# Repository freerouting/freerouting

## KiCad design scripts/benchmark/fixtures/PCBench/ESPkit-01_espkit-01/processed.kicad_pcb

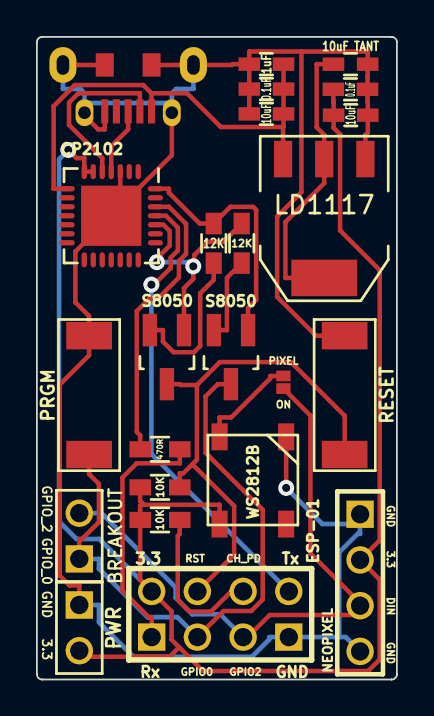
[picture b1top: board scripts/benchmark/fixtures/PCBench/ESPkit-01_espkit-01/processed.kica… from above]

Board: 2 copper layers, 20.0 x 35.7 mm, 24 parts (0 on the bottom side), 18 nets.

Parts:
C1, C6: 10uF; C_0603_HandSoldering
C4, C7: 0.1uF; C_0603_HandSoldering
C5: 1uF; C_0603_HandSoldering
C8: 10uF TANT; C_0603_HandSoldering
IC1: WS2812B; ws2812b
P1: ESP-01
P2: BREAKOUT; PIN_ARRAY_2X1
P3: USB_5PIN_SHELL; USB-MICRO-5pin_PTHMOUNT
P4: PWR; PIN_ARRAY_2X1
P5: NEOPIXEL; PIN_ARRAY_4x1
P6: BRIDGE; 603_bridge
Q1, Q2: S8050; SOT-23_Handsoldering
R1, R4: 10K; R_0603_HandSoldering
R2, R3: 12K; R_0603_HandSoldering
R5: 470R; R_0603_HandSoldering
SW1: RESET; 1107G
SW2: PRGM; 1107G
U1: LD1117; SOT-223
U2: CP2102; QFN-28-1EP_5x5mm_Pitch0.5mm

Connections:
+3.3V: C1.1, C4.1, IC1.1, P1.2, P4.2, P5.2, R1.2, R4.2, U2.6, U2.7
+3V3: C8.1, U1.2, U1.4
+5V: C5.1, C6.1, C7.1, P3.1, U1.3, U2.8
/DTR: Q2.1, R2.2, U2.28
/ESP_EN: P1.6, R1.1
/GPIO0: P1.3, P2.1, Q2.3, SW2.1
/GPIO2: P1.5, P2.2, P5.3, P6.2
/RESET: P1.4, Q1.3, R4.1, SW1.1
/RTS: Q1.1, R3.2, U2.24
/RXD: P1.8, U2.25
/TXD: P1.1, R5.1
/USB_D+: P3.3, U2.4
/USB_D-: P3.2, U2.5
GND: C1.2, C4.2, C5.2, C6.2, C7.2, C8.2, IC1.3, P1.7, P3.5, P3.SHLD, P4.1, P5.1, P5.4, SW1.2, SW2.2, U1.1, U2.3, U2.29
unnamed: IC1.4, P6.1
unnamed: Q1.2, R2.1
unnamed: Q2.2, R3.1
unnamed: R5.2, U2.26

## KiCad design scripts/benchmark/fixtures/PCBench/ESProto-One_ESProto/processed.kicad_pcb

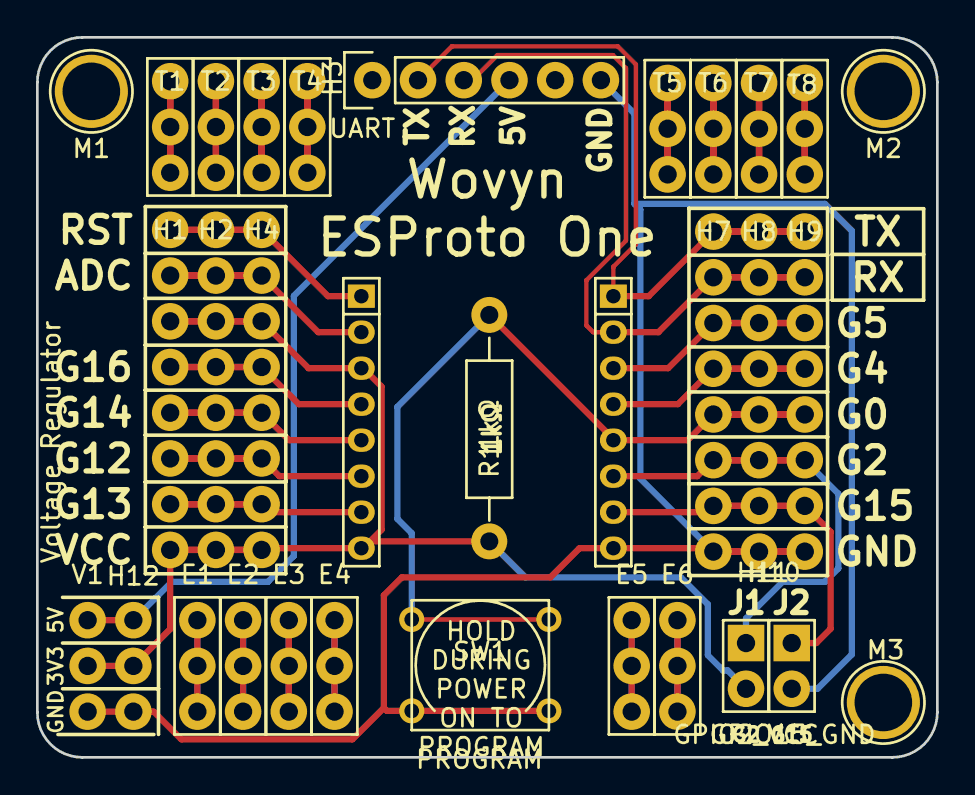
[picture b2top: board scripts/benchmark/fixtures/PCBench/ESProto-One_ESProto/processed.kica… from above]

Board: 2 copper layers, 50.0 x 40.0 mm, 32 parts (0 on the bottom side), 30 nets.

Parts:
E1: Ex1; Pin_Header_Straight_1x03
E2: Ex2; Pin_Header_Straight_1x03
E3: Ex3; Pin_Header_Straight_1x03
E4: Ex4; Pin_Header_Straight_1x03
E5: Ex5; Pin_Header_Straight_1x03
E6: Ex6; Pin_Header_Straight_1x03
H1: L3; Pin_Header_Straight_1x08
H2: L2; Pin_Header_Straight_1x08
H3: UART; Pin_Header_Straight_1x06
H4: L1; Pin_Header_Straight_1x08
H5: L0; Pin_Header_Straight_1x08_Pitch2.00mm
H6: R0; Pin_Header_Straight_1x08_Pitch2.00mm
H7: R1; Pin_Header_Straight_1x08
H8: R2; Pin_Header_Straight_1x08
H9: R3; Pin_Header_Straight_1x08
H10: GPIO15_GND; Pin_Header_Straight_1x02
H11: GPIO2_VCC; Pin_Header_Straight_1x02
H12: VRegOut; Pin_Header_Straight_1x03
M1, M2, M3: 1pin
R1: 1kΩ; Resistor_Horizontal_RM15mm
SW1: PROGRAM; SW_PUSH_SMALL
T1: T1; Pin_Header_Straight_1x03
T2: T2; Pin_Header_Straight_1x03
T3: T3; Pin_Header_Straight_1x03
T4: T4; Pin_Header_Straight_1x03
T5: T5; Pin_Header_Straight_1x03
T6: T6; Pin_Header_Straight_1x03
T7: T7; Pin_Header_Straight_1x03
T8: T8; Pin_Header_Straight_1x03
V1: Voltage_Regulator; Pin_Header_Straight_1x03

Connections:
+3V3: H1.3, H1.8, H2.3, H2.8, H4.3, H4.8, H5.3, H5.8, H11.2, H12.2, R1.1, V1.2
+5V: H3.4, H12.1, V1.1
GND: H3.6, H6.8, H7.8, H8.8, H9.8, H10.2, H12.3, SW1.2, V1.3
unnamed: E1.1, E1.2, E1.3
unnamed: E2.1, E2.2, E2.3
unnamed: E3.1, E3.2, E3.3
unnamed: E4.1, E4.2, E4.3
unnamed: E5.1, E5.2, E5.3
unnamed: E6.1, E6.2, E6.3
unnamed: H1.1, H2.1, H4.1, H5.1
unnamed: H1.2, H2.2, H4.2, H5.2
unnamed: H1.4, H2.4, H4.4, H5.4
unnamed: H1.5, H2.5, H4.5, H5.5
unnamed: H1.6, H2.6, H4.6, H5.6
unnamed: H1.7, H2.7, H4.7, H5.7
unnamed: H6.3, H7.3, H8.3, H9.3
unnamed: H6.4, H7.4, H8.4, H9.4
unnamed: H6.5, H7.5, H8.5, H9.5, R1.2, SW1.1
unnamed: H6.7, H7.7, H8.7, H9.7, H10.1
unnamed: H6.6, H7.6, H8.6, H9.6, H11.1
unnamed: T1.1, T1.2, T1.3
unnamed: T2.1, T2.2, T2.3
unnamed: T3.1, T3.2, T3.3
unnamed: T4.1, T4.2, T4.3
unnamed: T5.1, T5.2, T5.3
unnamed: T6.1, T6.2, T6.3
unnamed: T7.1, T7.2, T7.3
unnamed: T8.1, T8.2, T8.3
RXD: H3.3, H6.2, H7.2, H8.2, H9.2
TXD: H3.2, H6.1, H7.1, H8.1, H9.1

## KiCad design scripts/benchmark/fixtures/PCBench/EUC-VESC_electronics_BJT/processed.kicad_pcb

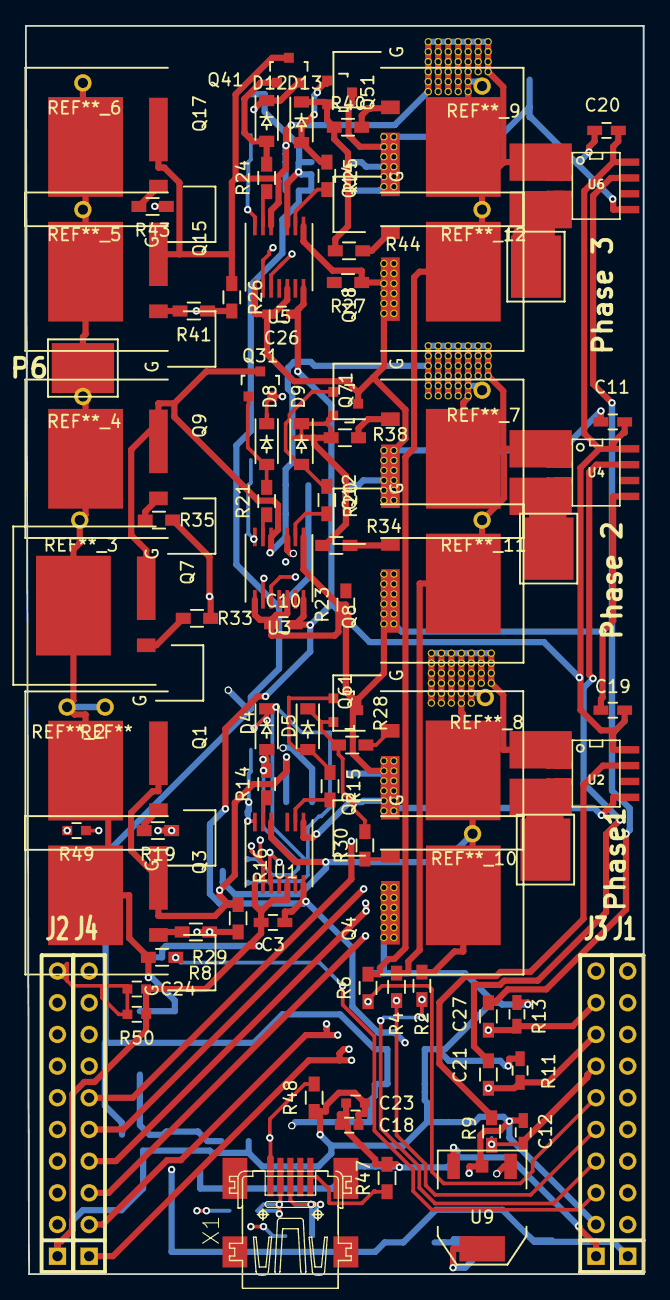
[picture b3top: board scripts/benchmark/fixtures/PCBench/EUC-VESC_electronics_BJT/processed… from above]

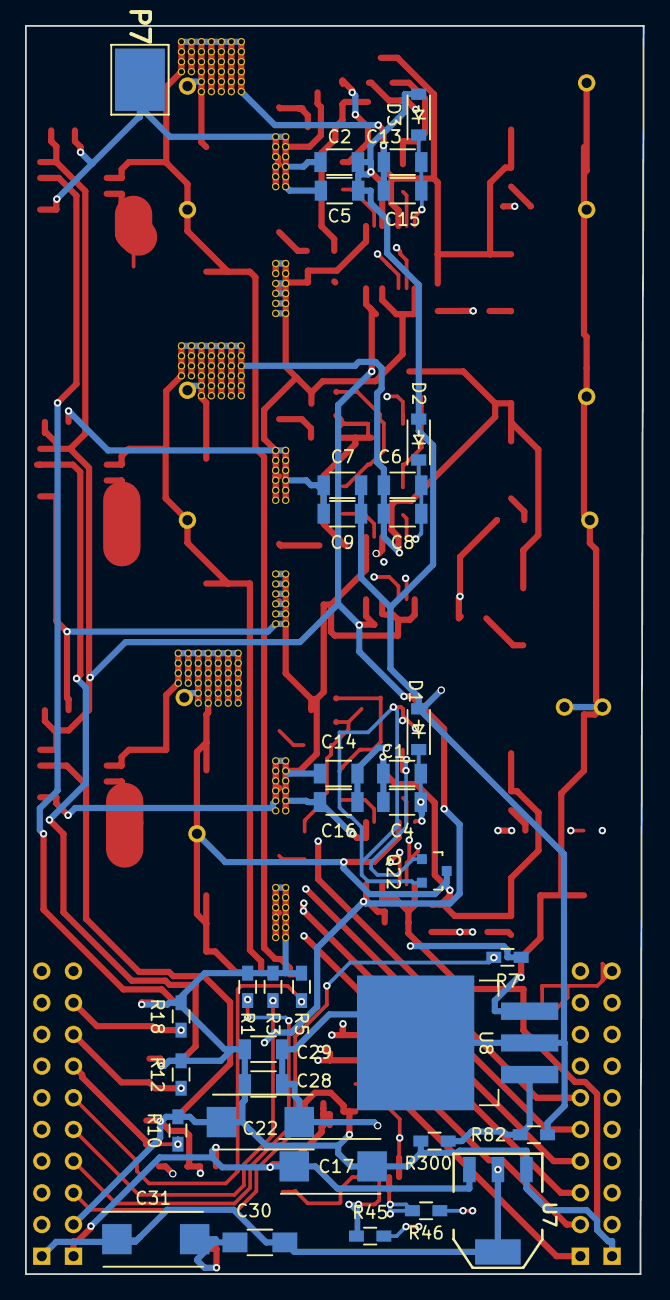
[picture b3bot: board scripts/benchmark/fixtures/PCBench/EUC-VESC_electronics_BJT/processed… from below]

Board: 4 copper layers, 49.5 x 100.1 mm, 120 parts (36 on the bottom side), 68 nets.

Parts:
C1, C2, C6, C7, C13, C14: 0.1uf; C_1206
C3, C10, C11, C12, C19, C20, C21, C26, C27: 0.1uf; C_0603_HandSoldering
C4, C5, C8, C9, C15, C16, C28, C29: 10uf; C_1206
C17, C22, C31: 100uf; TantalC_SizeD_EIA-7343_Reflow
C18, C23, C24: 10uf; C_0603
C30: 2.2uf; C_1206_HandSoldering
D1, D2, D3: DFLS1150-7; SOD-123
D4, D5, D8, D9, D12, D13: D_Schottky_Small; SOD-123
J1: Ti_Booster_40_J1; SIL-10J1
J2: Ti_Booster_40_J2; SIL-10J2
J3: Ti_Booster_40_J3; SIL-10J3
J4: Ti_Booster_40_J4; SIL-10J4
P6: IN+; 1PAD_4x5mm
P7: IN-; 1PAD_4x5mm
Phase1: MOTOR3; 1PAD_4x5mm
Phase 2: MOTOR2; 1PAD_4x5mm
Phase 3: MOTOR1; 1PAD_4x5mm
Q1, Q2, Q3, Q4, Q7, Q8, Q9, Q12, Q14, Q15, Q17, Q18: FDMT-800; PQFN-8L-FET
Q22, Q31, Q41, Q51, Q61, Q71: BC807-40; SOT-23
R1, R3, R5, R7: 1.3K; R_0603_HandSoldering
R2, R4, R6, R8: 39K; R_0603_HandSoldering
R9, R11, R13: 2k; R_0603_HandSoldering
R10, R12, R18: 3.9k; R_0603_HandSoldering
R14, R15, R20, R21, R24, R25: 10R; R_0603_HandSoldering
R16, R23, R26, R27: 39k; R_0603_HandSoldering
R19, R28, R29, R30, R33, R34, R35, R38, R40, R41, R43, R44, R45, R46: R22; R_0603_HandSoldering
R47: R0; R_0603_HandSoldering
R48: r0; R_0603_HandSoldering
R49: NTC10K; C_0603
R50: 10K; C_0603
R82: R; R_0603_HandSoldering
R300: R_Small; R_0603_HandSoldering
U1, U3, U5: ADuM7223; LGA-13
U2, U4, U6: ACS723; ACS723_40
U7: NCP1117ST33T3G; SOT-223
U8: tl783; TO-263-3Lead
U9: LM340MPX-5; SOT-223
X1: MINI-USB-SCHIELD-32005-201; con-cypressindustries-32005-201

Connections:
+3V3: C30.1, C31.1, J1.1, R49.1, U7.2
+5V: C3.2, C10.2, C11.1, C17.1, C18.1, C19.2, C20.1, C23.1, C26.1, J3.1, R47.2, U1.7, U2.8, U3.7, U4.8, U5.7, U6.8, U7.3, U9.3
/Power MOSFETS/CurrentA: C12.1, J3.7, R9.2, R10.1
/Power MOSFETS/CurrentB: C21.1, J3.8, R11.2, R12.1
/Power MOSFETS/CurrentC: C27.1, J3.9, R13.2, R18.1
/Power MOSFETS/H1_VS: C1.2, C4.2, Q1.2, Q2.1, Q3.2, Q4.1, Q22.3, R2.2, R16.1, U1.11, U2.1, U2.2
/Power MOSFETS/H2_VS: C6.2, C8.2, Q7.2, Q8.1, Q9.2, Q12.1, Q31.3, R4.2, U3.11, U4.1, U4.2
/Power MOSFETS/H3_VS: C13.2, C15.2, Q14.1, Q15.2, Q17.2, Q18.1, Q41.3, R6.2, R26.1, U5.11, U6.1, U6.2
/Power MOSFETS/M_H1: J4.1, U1.2
/Power MOSFETS/M_H2: J4.3, U3.2
/Power MOSFETS/M_H3: J4.5, U5.2
/Power MOSFETS/M_L1: J4.2, U1.3
/Power MOSFETS/M_L2: J4.4, U3.3
/Power MOSFETS/M_L3: J4.6, U5.3
/Power MOSFETS/PHASE_1: Phase1.1, U2.3, U2.4
/Power MOSFETS/PHASE_2: Phase 2.1, U4.3, U4.4
/Power MOSFETS/PHASE_3: Phase 3.1, U6.3, U6.4
GND: C2.2, C3.1, C5.2, C7.2, C9.2, C10.1, C11.2, C12.2, C14.2, C16.2, C17.2, C18.2, C19.1, C20.2, C21.2, C22.2, C23.2, C24.1, C26.2, C27.2, C28.1, C29.1, C30.2, C31.2, J2.1, J3.2, P7.1, Q2.2, Q4.2, Q8.2, Q12.2, Q14.2, Q18.2, Q51.3, Q61.3, Q71.3, R1.1, R3.1, R5.1, R7.1, R10.2, R12.2, R18.2, R23.1, R27.1, R48.1, R50.1, R300.2, U1.1, U1.5, U1.8, U2.5, U3.1, U3.5, U3.8, U4.5, U5.1, U5.5, U5.8, U6.5, U7.1, U9.2, U9.4
unnamed: C1.1, C4.1, D1.1, U1.13
unnamed: C6.1, C8.1, D2.1, U3.13
unnamed: C13.1, C15.1, D3.1, U5.13
unnamed: C24.2, J2.10, R49.2, R50.2
unnamed: D4.1, Q22.2, R16.2, R19.1, R29.1
unnamed: D4.2, Q22.1, R14.2
unnamed: D5.1, Q61.2, R28.2, R30.2
unnamed: D5.2, Q61.1, R15.1
unnamed: D8.1, Q31.2, R33.1, R35.1
unnamed: D8.2, Q31.1, R21.2
unnamed: D9.1, Q71.2, R34.1, R38.1
unnamed: D9.2, Q71.1, R20.1
unnamed: D12.1, Q41.2, R26.2, R41.1, R43.1
unnamed: D12.2, Q41.1, R24.2
unnamed: D13.1, Q51.2, R40.1, R44.1
unnamed: D13.2, Q51.1, R25.1
unnamed: J2.2, J2.3, R45.2
unnamed: J2.4, J2.5, R46.1
unnamed: J3.3, R7.2, R8.1
unnamed: J3.4, R1.2, R2.1
unnamed: J3.5, R3.2, R4.1
unnamed: J3.6, R5.2, R6.1
unnamed: Q1.3, R19.2
unnamed: Q2.3, R28.1
unnamed: Q3.3, R29.2
unnamed: Q4.3, R30.1
unnamed: Q7.3, R33.2
unnamed: Q8.3, R34.2
unnamed: Q9.3, R35.2
unnamed: Q12.3, R38.2
unnamed: Q14.3, R40.2
unnamed: Q15.3, R41.2
unnamed: Q17.3, R43.2
unnamed: Q18.3, R44.2
unnamed: R9.1, U2.7
unnamed: R11.1, U4.7
unnamed: R13.1, U6.7
unnamed: R14.1, U1.12
unnamed: R15.2, U1.9
unnamed: R20.2, U3.9
unnamed: R21.1, U3.12
unnamed: R24.1, U5.12
unnamed: R25.2, U5.9
unnamed: R45.1, X1.3
unnamed: R46.2, X1.2
unnamed: R47.1, X1.5
unnamed: R48.2, X1.1
unnamed: R82.2, R300.1, U8.1
VDD: C2.1, C5.1, C7.1, C9.1, C14.1, C16.1, C22.1, C28.2, C29.2, D1.2, D2.2, D3.2, R82.1, U3.10, U5.10, U8.2, U8.4, U9.1
V_SUPPLY: P6.1, Q1.1, Q3.1, Q7.1, Q9.1, Q15.1, Q17.1, R8.2, U8.3
